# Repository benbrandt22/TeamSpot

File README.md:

# TeamSpot

Hardware Mute Control for Microsoft Teams

(Currently a work in progress)

## Why does this exist?

This project was created because it seemed like a fun idea for a small electronics project to try some new things. In my professional life, I use Microsoft Teams for meetings and calls. During most meetings I try to have good microphone etiquette, muting myself when I'm not speaking to minimize background noise and distractions for others. When I wanted to speak, I didn't like having to grab my mouse and find the un-mute button. Sometimes that meant extra seconds of silence before I could respond. Sometimes I'd forget I'm on mute because I had another appication active. Keyboard shortcuts didn't seem like the right solution either, as sometimes I'm using another application that's active in front of MS Teams. I was in the mood to build some hardware, so a physical button seemed like the right way to handle this.

The other key objective was to get good visual feedback of my microphone's current mute status. I wanted the device to reflect the actual status of the microphone in Teams, so that if I muted myself using the software controls, the device would show that as well.

## Hardware

- [Firmware ReadMe](src/firmware/README.md)
- [Circuit Board ReadMe](src/board/README.md)

# Software

- [Windows Service ReadMe](src/service/README.md)

## Teams Integration

My initial research revealed a local websocket API that published realtime events from Teams, and had the ability to send commands to Teams. This was originally released (I think) around 2023 and was heavily used by the Elgato Stream Deck to allow similar control and status display integration with Teams.

This local Teams API can be seen in MS Teams under Settings > Privacy > Third-Party app API.

Some related links:
- https://techcommunity.microsoft.com/blog/microsoftteamsblog/delivering-new-webinar-experiences-with-microsoft-teams/3725145
- https://github.com/malkstar/ms_teams_websockets
- https://github.com/svrooij/teams-monitor/issues/15
- https://github.com/svrooij/teams-monitor
- https://support.microsoft.com/en-us/office/connect-to-third-party-devices-in-microsoft-teams-aabca9f2-47bb-407f-9f9b-81a104a883d6?wt.mc_id=SEC-MVP-5004985
- https://lostdomain.notion.site/Microsoft-Teams-WebSocket-API-5c042838bc3e4731bdfe679e864ab52a

When I discovered this, I also found articles/posts that revealed that Microsoft was planning on deprecating and/or removing this API, announced in late 2025. The Teams instance on my personal computer did not have this API enabled. However, my Teams installation on my work laptop did have it enabled. They were both on the same version, so something about my corporate account had this feature enabled. It could still go away someday, but for now it works and that's good enough for my little project.

_UPDATE August 2026 - The third-party API settings are now missing from my Teams installation. It would seem that Microsoft finally actually deprecated the feature. It may be time to explore other ways to get status and control the microphone_

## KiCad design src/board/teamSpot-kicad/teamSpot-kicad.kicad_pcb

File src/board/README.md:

# Circuit Board

The circuit board was designed with [KiCad](https://www.kicad.org/). I've designed boards in the past with other tools, and this was my first project in KiCad. With a little help from YouTube tutorials, I was able to get up to speed quickly.

The board contains a mix of surface mount and through-hole components. The RGB LEDs, capacitors, and resistor are all surface mount, while the microcontroller and keyboard switch are through-hole.

The schematic was inspired by the [Adafruit Neopixel Jewel](https://www.adafruit.com/product/2226), which uses a similar circuit to control RGB LEDs. The board arranges 6 WS2812B LEDs in a circular pattern, with a single data line running through each LED. The keyboard switch is soldered to the front of the board in the middle of the LEDs.

The microcontroller is mounted on the back of the board, offset from the board using pin headers/sockets. The five pins opposite of the USB plug are not included in the board design. They are not used in the circuit, and removing them leaves space to mount the keyboard switch.

Two 3mm mounitng holes are included to allow two M3 bolts to hold the board in place.

For my personal build, I ordered boards from [PCBWay](https://www.pcbway.com/) mainly for their hobbyist-friendly pricing. They also provide a KiCad plugin that makes it easy to export and upload design files and order the boards online.

## Useful Links:

- [KiCad](https://www.kicad.org/)
- [Adafruit Neopixel Jewel](https://www.adafruit.com/product/2226)
- [Neopixel Schematics and PCBs](https://learn.adafruit.com/adafruit-neopixel-uberguide/downloads)
- [RP2040-Zero Symbol/Footprint Download](https://www.snapeda.com/parts/RP2040-ZERO/Waveshare%20Electronics/view-part/)
- [PCBWay](https://www.pcbway.com/)
- [PCBWay KiCad Plugin Info](https://www.pcbway.com/blog/News/PCBWay_Plug_In_for_KiCad_3ea6219c.html)

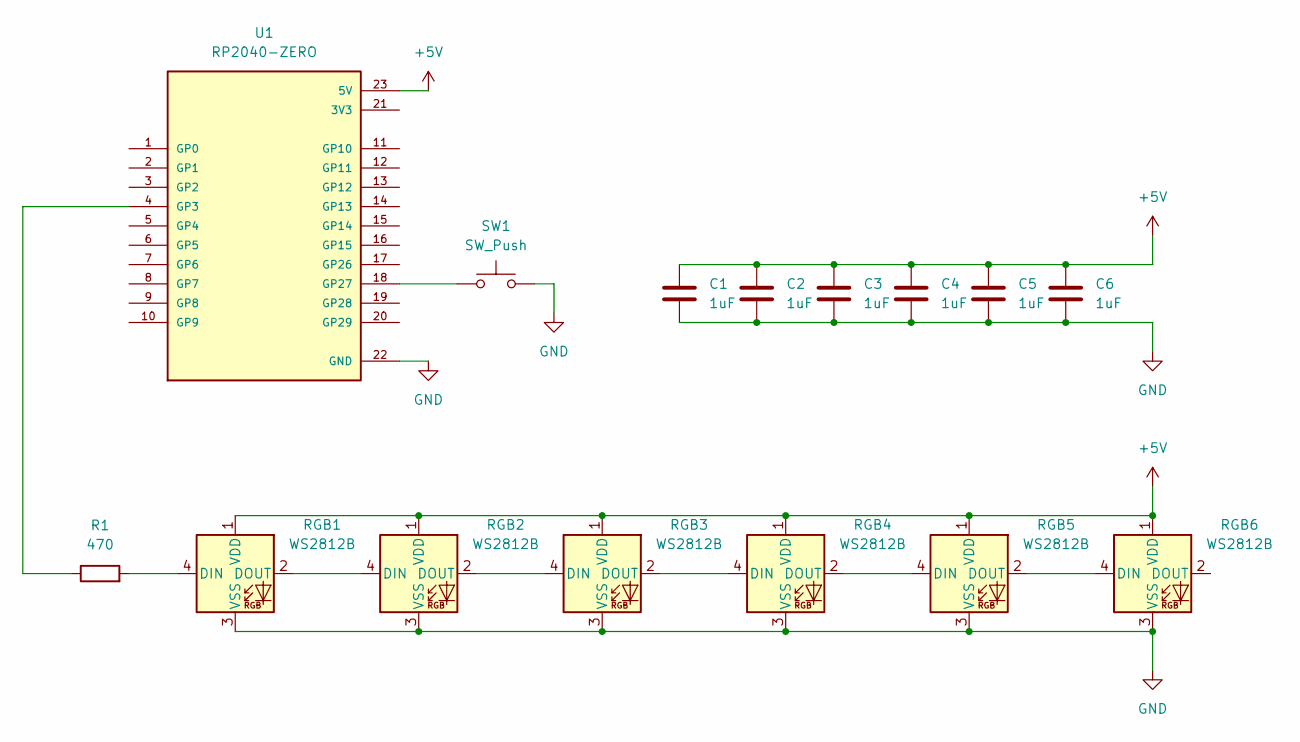
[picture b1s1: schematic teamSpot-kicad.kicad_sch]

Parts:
C1, C2, C3, C4, C5, C6: 1uF; C_0603_1608Metric
R1: 470; R_0603_1608Metric
RGB1, RGB2, RGB3, RGB4, RGB5, RGB6: WS2812B; LED_WS2812B_PLCC4_5.0x5.0mm_P3.2mm
SW1: SW_Push; SW_Cherry_MX_1.00u_PCB
U1: RP2040-ZERO; MODULE_RP2040-ZERO-SIDES-ONLY; PARTREV NA

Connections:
+5V: C1.1, C2.1, C3.1, C4.1, C5.1, C6.1, RGB1.1 (VDD), RGB2.1 (VDD), RGB3.1 (VDD), RGB4.1 (VDD), RGB5.1 (VDD), RGB6.1 (VDD), U1.23 (5V)
GND: C1.2, C2.2, C3.2, C4.2, C5.2, C6.2, RGB1.3 (VSS), RGB2.3 (VSS), RGB3.3 (VSS), RGB4.3 (VSS), RGB5.3 (VSS), RGB6.3 (VSS), SW1.2, U1.22 (GND)
unnamed: R1.2, RGB1.4 (DIN)
unnamed: RGB1.2 (DOUT), RGB2.4 (DIN)
unnamed: RGB2.2 (DOUT), RGB3.4 (DIN)
unnamed: RGB3.2 (DOUT), RGB4.4 (DIN)
unnamed: RGB4.2 (DOUT), RGB5.4 (DIN)
unnamed: RGB5.2 (DOUT), RGB6.4 (DIN)
unnamed: R1.1, U1.4 (GP3)
unnamed: SW1.1, U1.18 (GP27)

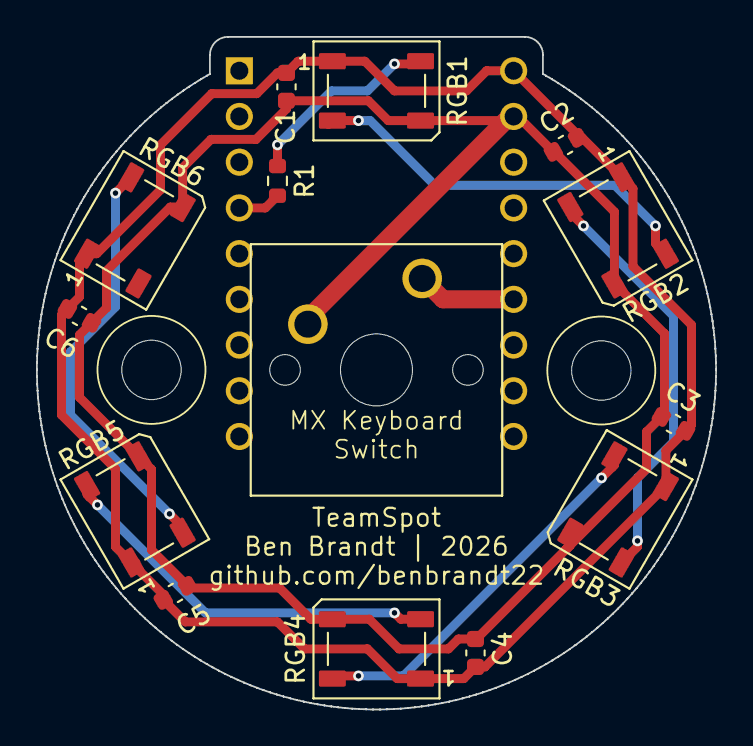
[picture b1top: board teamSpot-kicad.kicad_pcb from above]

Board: 2 copper layers, 37.7 x 37.4 mm, 15 parts (1 on the bottom side), 10 nets.

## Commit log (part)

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2026-05-12 Initial ReadMe and gitignore file
2026-05-12 Initial MVP device code with basic USB send/receive
2026-05-12 Added blank solution for service project
2026-05-13 established basic windows service that reads USB button presses
2026-05-14 Added Teams integration and basic LED on/off functionality
2026-05-15 Updated device to support RGB/brightness output
2026-05-15 Updated service to send LED color commands
2026-05-15 turn off LED at service shutdown
2026-05-15 Updated install script to include service config and startup
2026-05-20 Updated to support multiple neopixel LEDs, updated startup animation
2026-05-20 Added heartbeat signal to better recover from USB disconnects
2026-05-21 Added classes to represent button state change inputs
2026-05-21 Moved USB parsing logic into the event, built framework for parsing input events
2026-05-22 Updated pin assignments
2026-05-24 renamed folder
2026-05-29 Adds KiCad circuit board design
2026-06-09 Handles write failures and allows write loop to continue
2026-06-12 Updated pin assignments and LED count for circuit board
2026-06-14 disable USB storage access unless button is held at startup
2026-06-17 Updated secure settings service to use new filename based on class, renamed settings class for API token
2026-06-17 Set up configurable colors in appSettings
